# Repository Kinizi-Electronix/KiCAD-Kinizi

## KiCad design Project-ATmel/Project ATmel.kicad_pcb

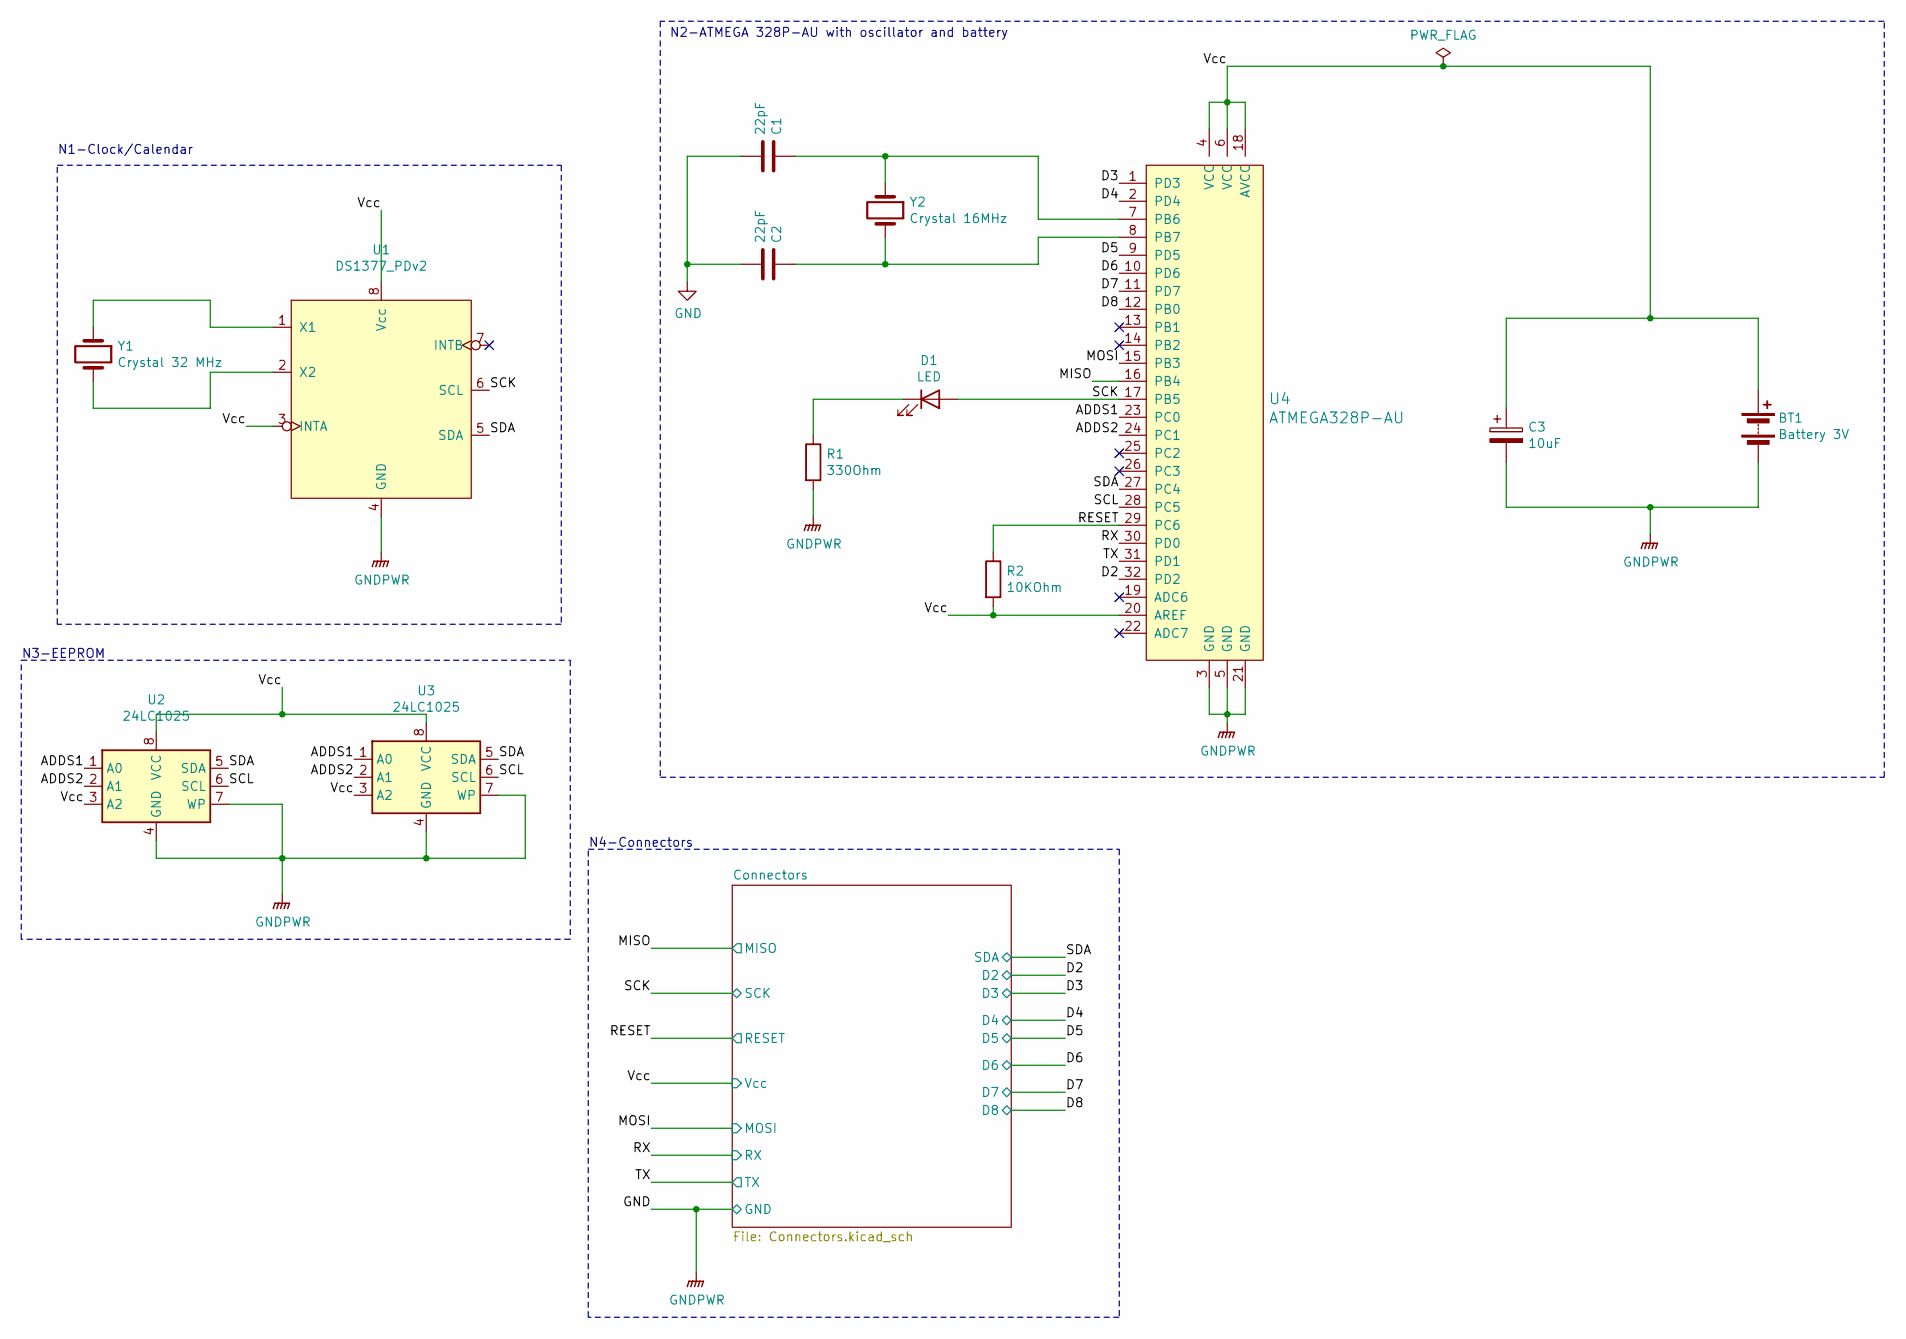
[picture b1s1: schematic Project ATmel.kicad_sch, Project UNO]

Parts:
BT1: Battery 3V; PinHeader_1x02_P2.54mm_Vertical
C1, C2: 22pF; C_0805_2012Metric_Pad1.15x1.40mm_HandSolder
C3: 10uF; C_0805_2012Metric_Pad1.15x1.40mm_HandSolder
D1: LED; LED_0805_2012Metric_Pad1.15x1.40mm_HandSolder
R1: 330Ohm; R_0805_2012Metric_Pad1.15x1.40mm_HandSolder
R2: 10KOhm; R_0805_2012Metric_Pad1.15x1.40mm_HandSolder
U1: DS1377_PDv2; SOIJ-8_5.3x5.3mm_P1.27mm
U2, U3: 24LC1025; SO-8_5.3x6.2mm_P1.27mm
U4: ATMEGA328P-AU; TQFP-32_7x7mm; MPN ATMEGA328P-AU; Digi-Key_PN ATMEGA328P-AU-ND
Y1: Crystal 32 MHz; Crystal_SMD_MicroCrystal_CC7V-T1A-2Pin_3.2x1.5mm_HandSolder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
Y2: Crystal 16MHz; Crystal_SMD_5032-2Pin_5.0x3.2mm_HandSoldering

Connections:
/ADDS1: U2.1 (A0), U3.1 (A0), U4.23 (PC0)
/ADDS2: U2.2 (A1), U3.2 (A1), U4.24 (PC1)
/D2: U4.32 (PD2); also elsewhere on the board
/D3: U4.1 (PD3); also elsewhere on the board
/D4: U4.2 (PD4); also elsewhere on the board
/D5: U4.9 (PD5); also elsewhere on the board
/D6: U4.10 (PD6); also elsewhere on the board
/D7: U4.11 (PD7); also elsewhere on the board
/D8: U4.12 (PB0); also elsewhere on the board
/MISO: U4.16 (PB4); also elsewhere on the board
/MOSI: U4.15 (PB3); also elsewhere on the board
/RESET: R2.1, U4.29 (PC6); also elsewhere on the board
/RX: U4.30 (PD0); also elsewhere on the board
/SCK: D1.2 (A), U1.6 (SCL), U4.17 (PB5); also elsewhere on the board
/SCL: U2.6 (SCL), U3.6 (SCL), U4.28 (PC5)
/SDA: U1.5 (SDA), U2.5 (SDA), U3.5 (SDA), U4.27 (PC4); also elsewhere on the board
/TX: U4.31 (PD1); also elsewhere on the board
/Vcc: BT1.1 (+), C3.1, R2.2, U1.3 (INTA), U1.8 (Vcc), U2.3 (A2), U2.8 (VCC), U3.3 (A2), U3.8 (VCC), U4.4 (VCC), U4.6 (VCC), U4.18 (AVCC), U4.20 (AREF); also elsewhere on the board
GND: BT1.2 (-), C1.1, C2.1, C3.2, R1.2, U1.4 (GND), U2.4 (GND), U2.7 (WP), U3.4 (GND), U3.7 (WP), U4.3 (GND), U4.5 (GND), U4.21 (GND); also elsewhere on the board
unnamed: C1.2, U4.7 (PB6), Y2.1
unnamed: C2.2, U4.8 (PB7), Y2.2
unnamed: D1.1 (K), R1.1
unnamed: U1.1 (X1), Y1.1
unnamed: U1.2 (X2), Y1.2

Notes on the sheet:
N3-EEPROM
N1-Clock/Calendar
N2-ATMEGA 328P-AU with oscillator and battery
N4-Connectors

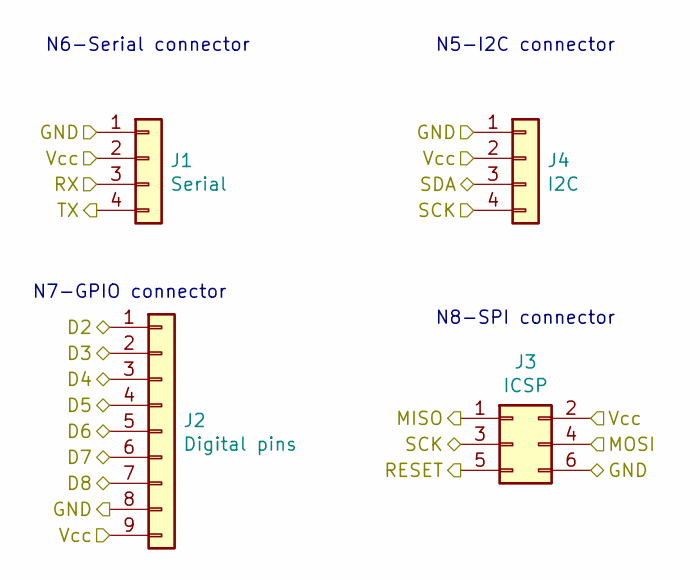
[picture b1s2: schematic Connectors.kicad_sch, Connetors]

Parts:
J1: Serial; PinSocket_1x04_P2.54mm_Vertical
J2: Digital pins; PinSocket_1x09_P2.54mm_Vertical
J3: ICSP; PinSocket_2x03_P2.54mm_Vertical
J4: I2C; PinSocket_1x04_P2.54mm_Vertical

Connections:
/D2: J2.1; also elsewhere on the board
/D3: J2.2; also elsewhere on the board
/D4: J2.3; also elsewhere on the board
/D5: J2.4; also elsewhere on the board
/D6: J2.5; also elsewhere on the board
/D7: J2.6; also elsewhere on the board
/D8: J2.7; also elsewhere on the board
/MISO: J3.1; also elsewhere on the board
/MOSI: J3.4; also elsewhere on the board
/RESET: J3.5; also elsewhere on the board
/RX: J1.3; also elsewhere on the board
/SCK: J3.3, J4.4; also elsewhere on the board
/SDA: J4.3; also elsewhere on the board
/TX: J1.4; also elsewhere on the board
/Vcc: J1.2, J2.9, J3.2, J4.2; also elsewhere on the board
GND: J1.1, J2.8, J3.6, J4.1; also elsewhere on the board

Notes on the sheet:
N6-Serial connector
N8-SPI connector
N7-GPIO connector
N5-I2C connector

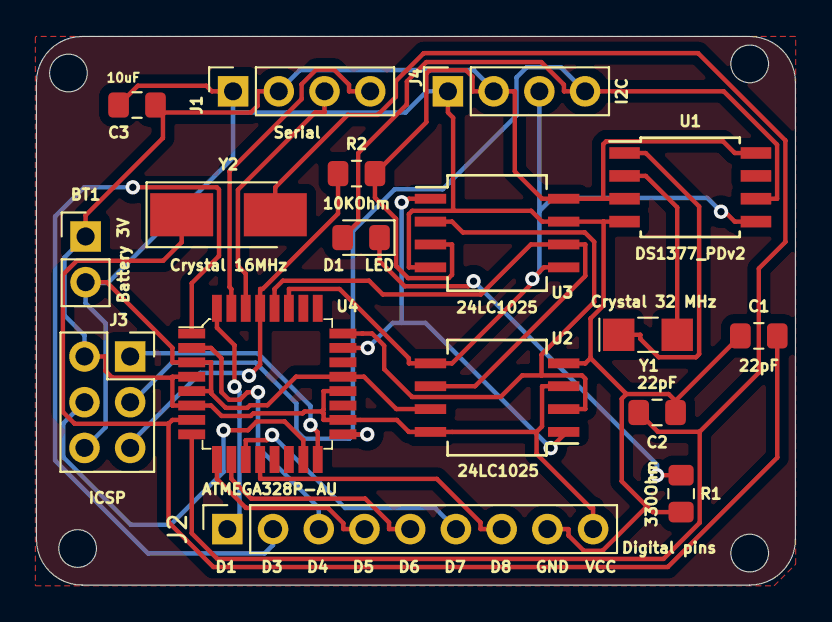
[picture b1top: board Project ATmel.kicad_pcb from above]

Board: 2 copper layers, 42.2 x 30.5 mm, 17 parts (0 on the bottom side), 24 nets.

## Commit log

2024-11-28 Create l
2024-11-28 Create First
